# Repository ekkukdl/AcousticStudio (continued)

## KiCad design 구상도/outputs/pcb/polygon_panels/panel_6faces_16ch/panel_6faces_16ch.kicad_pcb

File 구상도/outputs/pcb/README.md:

# PCB 설계 및 업체 제출 자료

## 현재 8면 8기판 32채널 구성

현재 개발 기준은 한 기판 32채널, 같은 기판 8장, 총 256송신기입니다. [32채널 PCB R1 제작 자료](../panel_8faces_32ch_R1/README.md)와 [프레임 포함 Creo R2](../panel_8faces_32ch_R1/mechanical/creo32_frame_R2/사용안내.md)를 사용하세요. 아래 16채널 기판 16장의 업체 제출 자료는 이전 구성으로 보존한 것입니다.

## 이전 8면 16기판 요청

한 기판 16채널, 동일 기판 총 16장, 송신기 총 256개 구성입니다.

- [전체 납땜 요청 안내](polygon_panels/pcba_8faces_16boards/README_업로드_및_납땜요청.md)
- [DOILLABS 업로드 사용 안내](polygon_panels/pcba_8faces_16boards/DOILLABS/사용안내.txt)
- [업로드 BOM CSV](polygon_panels/pcba_8faces_16boards/DOILLABS/DOILLABS_BOM_8faces_16ch_UPLOAD.csv)
- [업로드 PnP CSV](polygon_panels/pcba_8faces_16boards/DOILLABS/DOILLABS_PnP_8faces_16ch_UPLOAD.csv)
- [업로드 BOM XLSX](polygon_panels/pcba_8faces_16boards/DOILLABS/DOILLABS_BOM_8faces_16ch_UPLOAD.xlsx)
- [업로드 PnP XLSX](polygon_panels/pcba_8faces_16boards/DOILLABS/DOILLABS_PnP_8faces_16ch_UPLOAD.xlsx)
- [8면용 Gerber ZIP](polygon_panels/pcba_8faces_16boards/panel_8faces_16ch_Gerber_P0_quote.zip)

DOILLABS에는 안내에 따라 `*_UPLOAD` 파일을 사용하세요. CSV와 같은 내용의 XLSX를 중복 제출하지 마세요. 접미사 없는 기존 XLSX와 기존 견적 ZIP은 이전 작성본으로 보존했으며 최신 UPLOAD 파일을 포함한다고 간주하지 마세요. 초음파 송신기 등 THT는 별도 수삽 작업으로 요청해야 합니다.

## KiCad 원본과 초기안

- [6면용 기판 원본](polygon_panels/panel_6faces_16ch/)
- [8면용 기판 원본](polygon_panels/panel_8faces_16ch/)
- [설계 설명](polygon_panels/설계설명_및_확인방법.md)
- [초기 Gerber ZIP](polygon_panels/gerber_quotes/)
- [초기 부품 견적](polygon_panels/부품견적_6면_8면.md)
- [초기 제조 및 추가 구매품 견적](polygon_panels/제작및추가부품견적_센서제외.md)

KiCad 프로젝트와 전용 심볼·풋프린트·3D 모델은 함께 보존했습니다. 기존 견적은 6면 6장 / 8면 8장 기준입니다. 현재 P0 자료의 간격 경고와 부품 방향 검토는 제조 승인 전에 필요합니다.

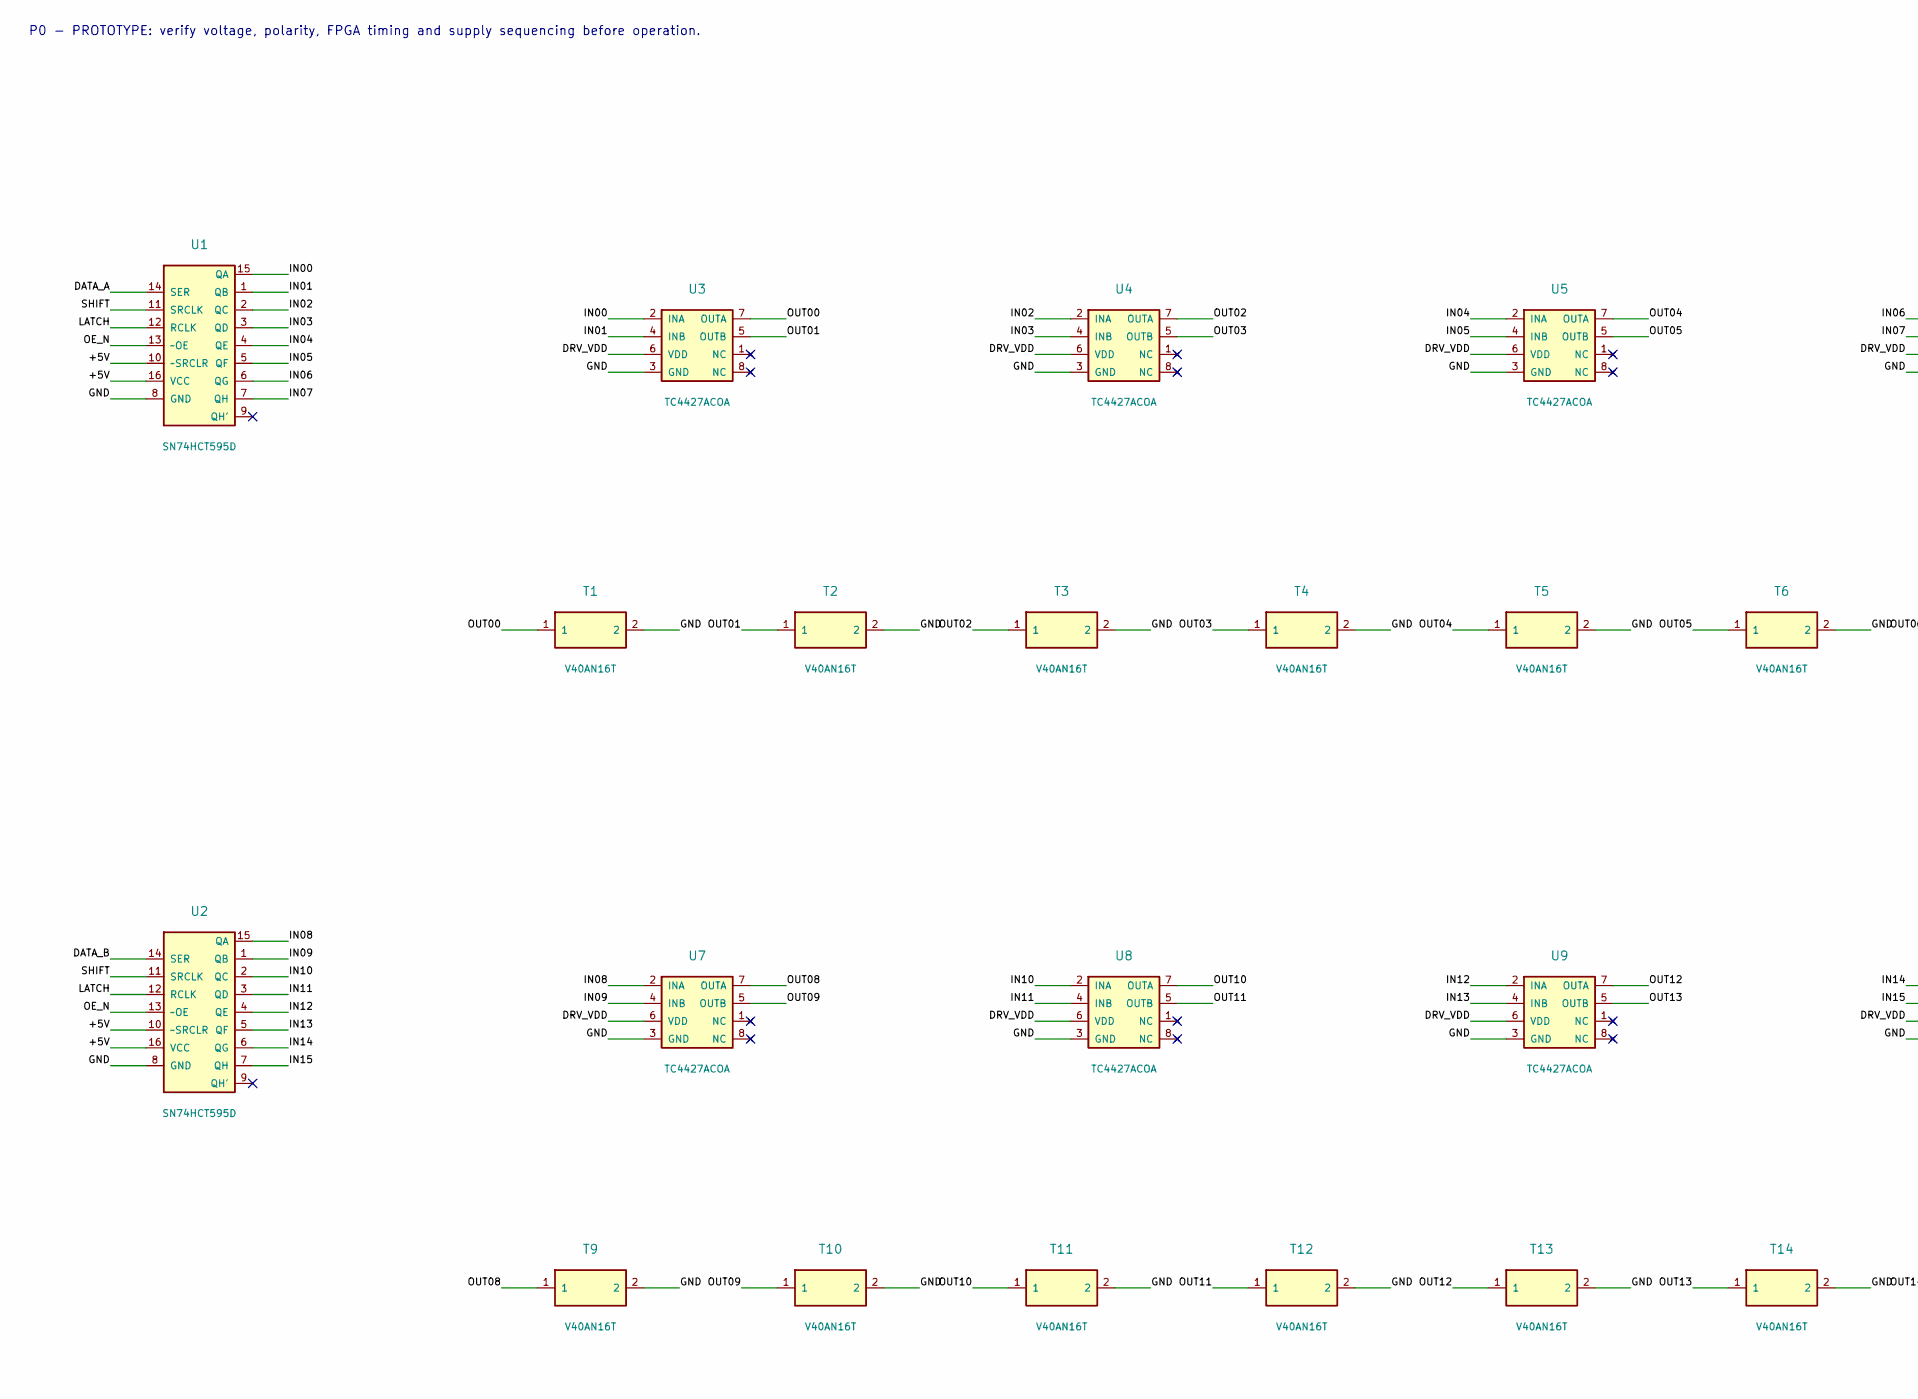
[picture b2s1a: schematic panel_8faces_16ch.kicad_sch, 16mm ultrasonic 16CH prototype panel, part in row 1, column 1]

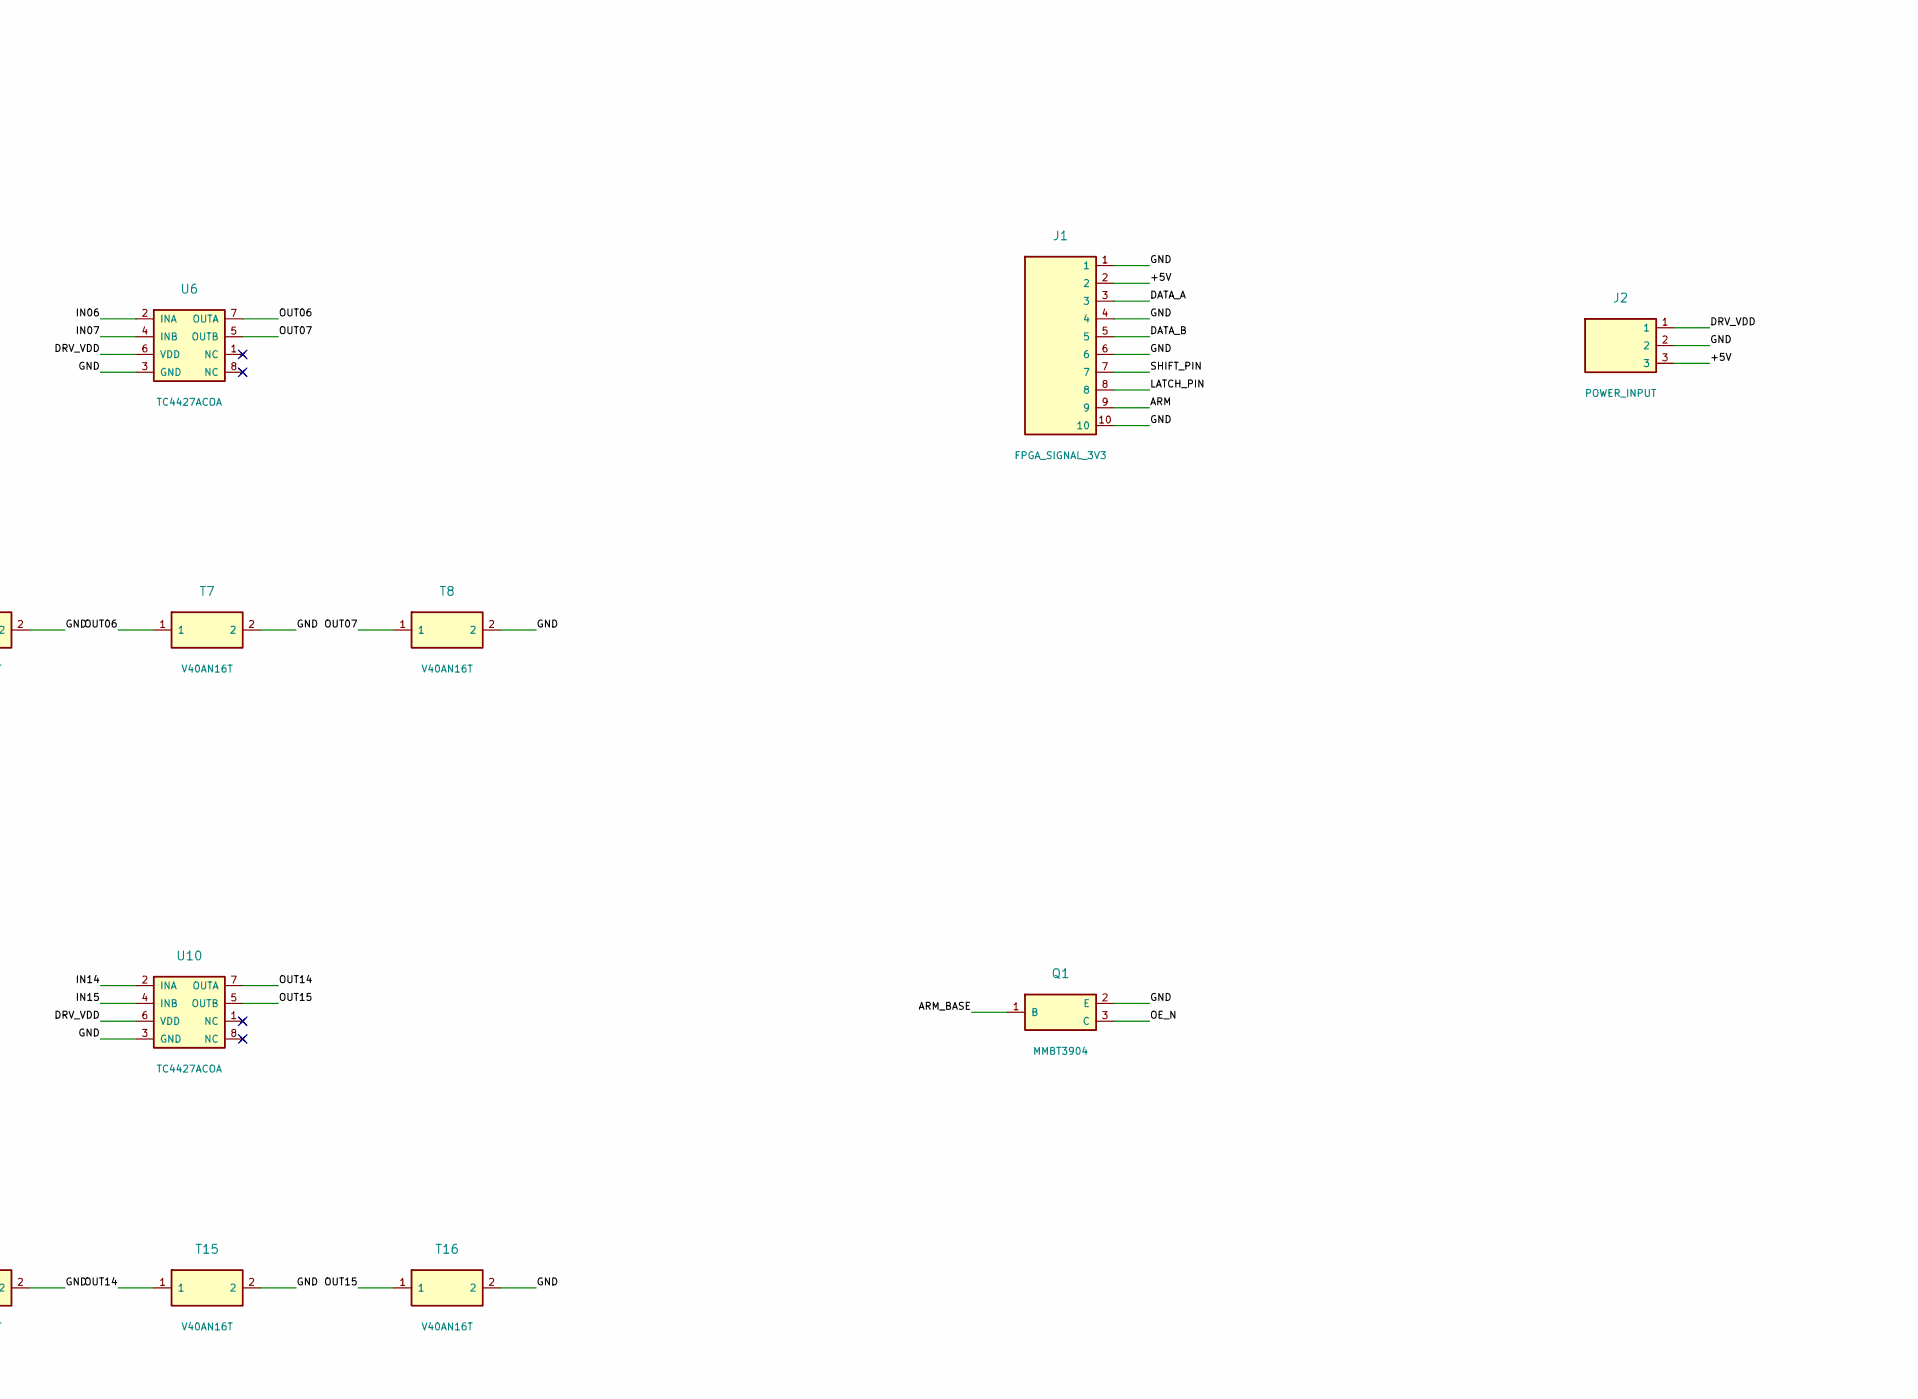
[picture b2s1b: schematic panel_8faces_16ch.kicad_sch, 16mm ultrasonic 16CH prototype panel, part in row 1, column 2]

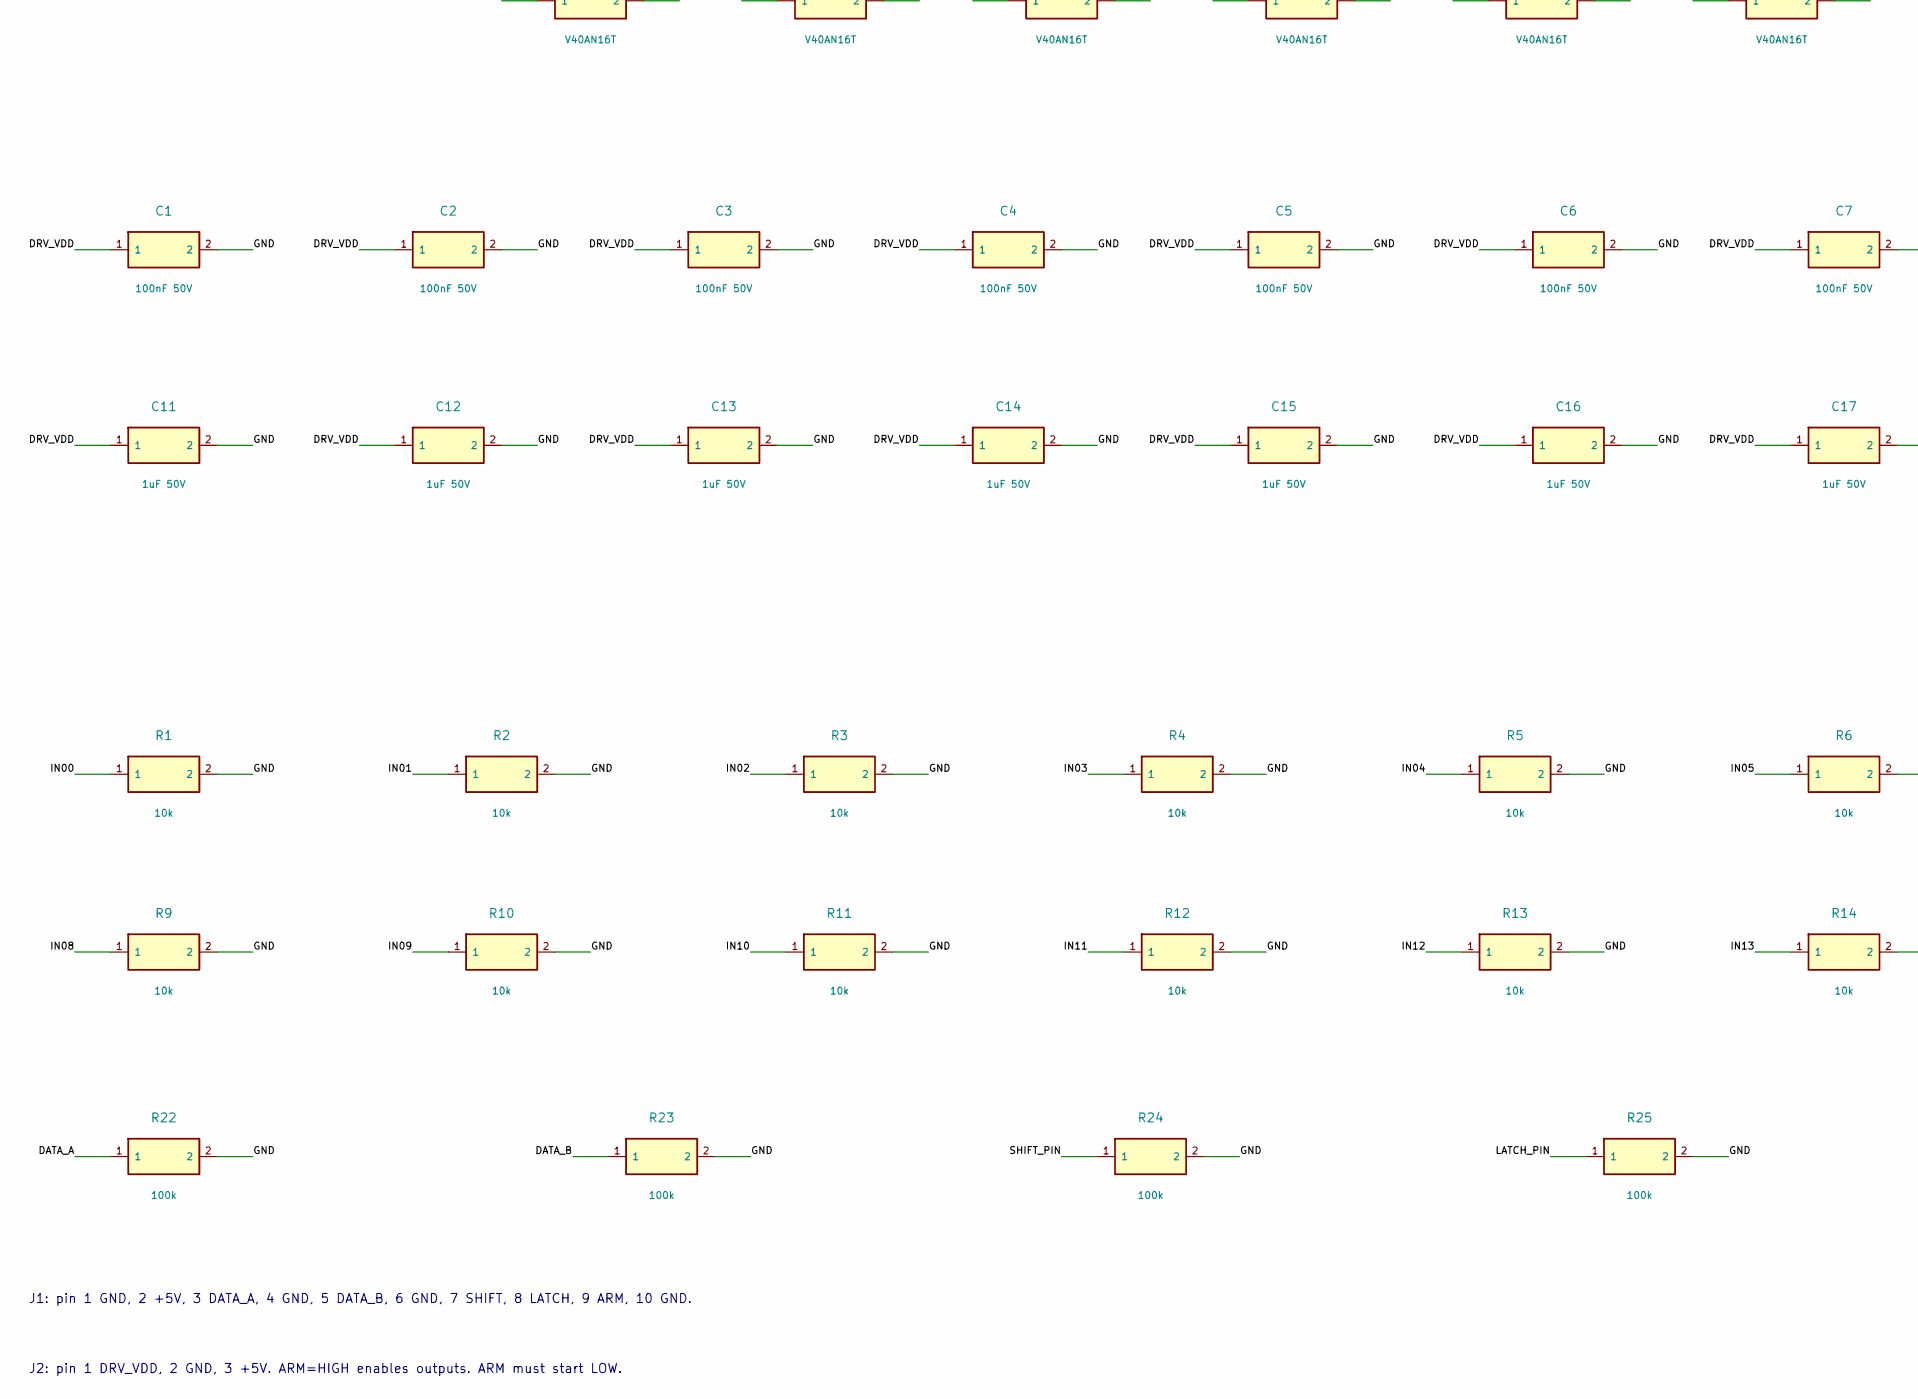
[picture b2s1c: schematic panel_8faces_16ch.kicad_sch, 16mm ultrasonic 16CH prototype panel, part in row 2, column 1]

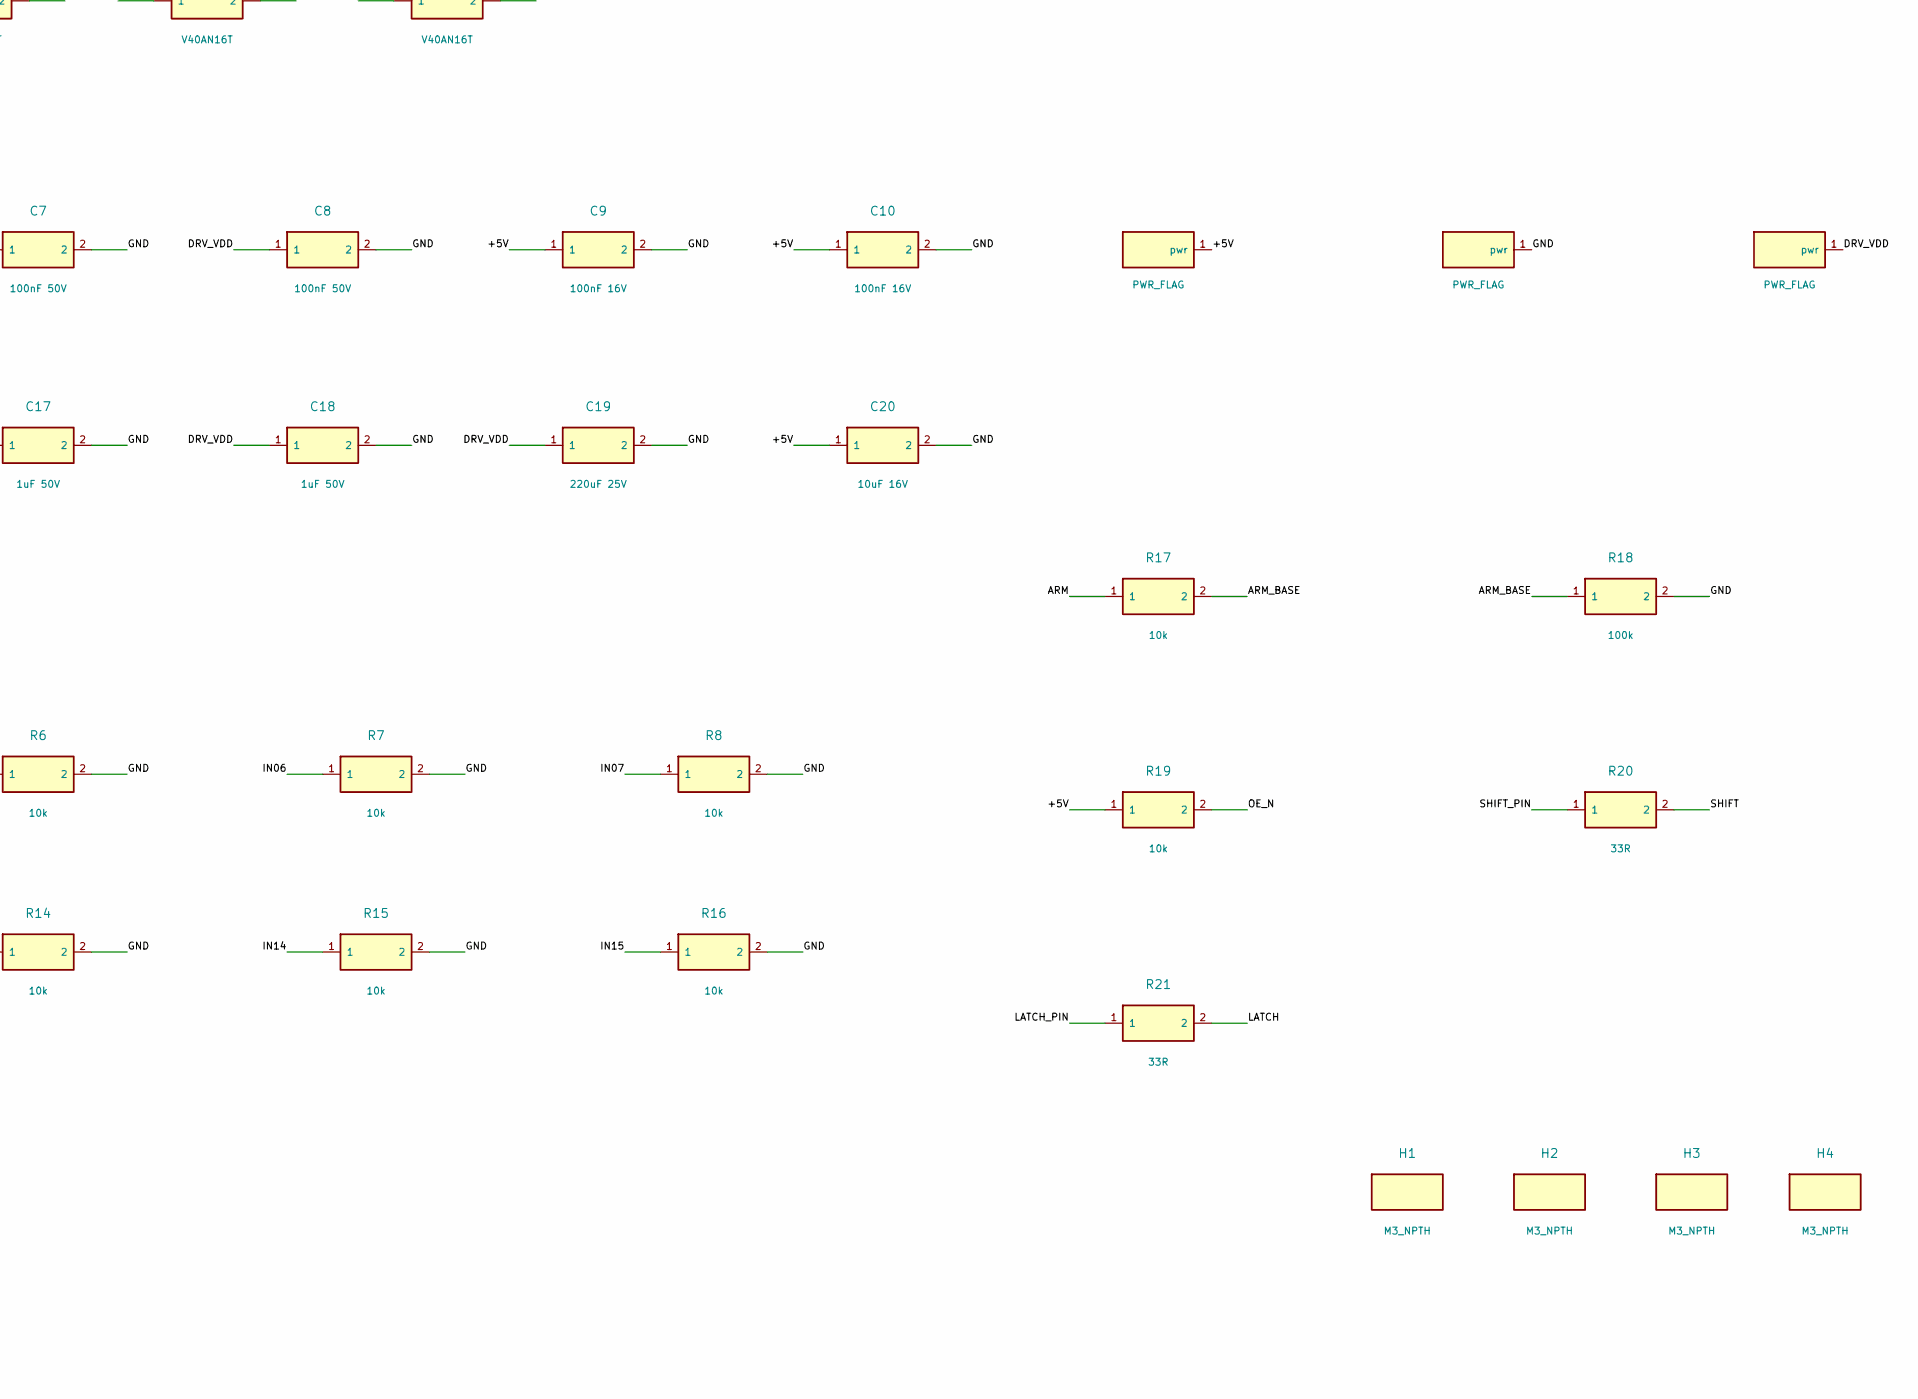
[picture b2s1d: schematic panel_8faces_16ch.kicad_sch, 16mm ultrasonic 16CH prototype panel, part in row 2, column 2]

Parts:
C1, C2, C3, C4, C5, C6, C7, C8: 100nF 50V; C0805
C9, C10: 100nF 16V; C0805
C11, C12, C13, C14, C15, C16, C17, C18: 1uF 50V; C0805
C19: 220uF 25V; CP_Radial_D6.3_P2.5
C20: 10uF 16V; C0805
H1, H2, H3, H4: M3_NPTH; Mount_M3
J1: FPGA_SIGNAL_3V3; Header2x05
J2: POWER_INPUT; Header1x03
Q1: MMBT3904; SOT23
R1, R2, R3, R4, R5, R6, R7, R8, R9, R10, R11, R12, R13, R14, R15, R16, R17, R19: 10k; R0805
R18, R22, R23, R24, R25: 100k; R0805
R20, R21: 33R; R0805
T1, T2, T3, T4, T5, T6, T7, T8, T9, T10, T11, T12, T13, T14, T15, T16: V40AN16T; V40AN16T_P10
U1, U2: SN74HCT595D; SOIC16
U3, U4, U5, U6, U7, U8, U9, U10: TC4427ACOA; SOIC8

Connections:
/+5V: C9.1, C10.1, C20.1, J1.2, J2.3, R19.1, U1.10 (~SRCLR), U1.16 (VCC), U2.10 (~SRCLR), U2.16 (VCC)
/ARM: J1.9, R17.1
/ARM_BASE: Q1.1 (B), R17.2, R18.1
/DATA_A: J1.3, R22.1, U1.14 (SER)
/DATA_B: J1.5, R23.1, U2.14 (SER)
/DRV_VDD: C1.1, C2.1, C3.1, C4.1, C5.1, C6.1, C7.1, C8.1, C11.1, C12.1, C13.1, C14.1, C15.1, C16.1, C17.1, C18.1, C19.1, J2.1, U3.6 (VDD), U4.6 (VDD), U5.6 (VDD), U6.6 (VDD), U7.6 (VDD), U8.6 (VDD), U9.6 (VDD), U10.6 (VDD)
/GND: C1.2, C2.2, C3.2, C4.2, C5.2, C6.2, C7.2, C8.2, C9.2, C10.2, C11.2, C12.2, C13.2, C14.2, C15.2, C16.2, C17.2, C18.2, C19.2, C20.2, J1.1, J1.4, J1.6, J1.10, J2.2, Q1.2 (E), R1.2, R2.2, R3.2, R4.2, R5.2, R6.2, R7.2, R8.2, R9.2, R10.2, R11.2, R12.2, R13.2, R14.2, R15.2, R16.2, R18.2, R22.2, R23.2, R24.2, R25.2, T1.2, T2.2, T3.2, T4.2, T5.2, T6.2, T7.2, T8.2, T9.2, T10.2, T11.2, T12.2, T13.2, T14.2, T15.2, T16.2, U1.8 (GND), U2.8 (GND), U3.3 (GND), U4.3 (GND), U5.3 (GND), U6.3 (GND), U7.3 (GND), U8.3 (GND), U9.3 (GND), U10.3 (GND)
/IN00: R1.1, U1.15 (QA), U3.2 (INA)
/IN01: R2.1, U1.1 (QB), U3.4 (INB)
/IN02: R3.1, U1.2 (QC), U4.2 (INA)
/IN03: R4.1, U1.3 (QD), U4.4 (INB)
/IN04: R5.1, U1.4 (QE), U5.2 (INA)
/IN05: R6.1, U1.5 (QF), U5.4 (INB)
/IN06: R7.1, U1.6 (QG), U6.2 (INA)
/IN07: R8.1, U1.7 (QH), U6.4 (INB)
/IN08: R9.1, U2.15 (QA), U7.2 (INA)
/IN09: R10.1, U2.1 (QB), U7.4 (INB)
/IN10: R11.1, U2.2 (QC), U8.2 (INA)
/IN11: R12.1, U2.3 (QD), U8.4 (INB)
/IN12: R13.1, U2.4 (QE), U9.2 (INA)
/IN13: R14.1, U2.5 (QF), U9.4 (INB)
/IN14: R15.1, U2.6 (QG), U10.2 (INA)
/IN15: R16.1, U2.7 (QH), U10.4 (INB)
/LATCH: R21.2, U1.12 (RCLK), U2.12 (RCLK)
/LATCH_PIN: J1.8, R21.1, R25.1
/OE_N: Q1.3 (C), R19.2, U1.13 (~OE), U2.13 (~OE)
/OUT00: T1.1, U3.7 (OUTA)
/OUT01: T2.1, U3.5 (OUTB)
/OUT02: T3.1, U4.7 (OUTA)
/OUT03: T4.1, U4.5 (OUTB)
/OUT04: T5.1, U5.7 (OUTA)
/OUT05: T6.1, U5.5 (OUTB)
/OUT06: T7.1, U6.7 (OUTA)
/OUT07: T8.1, U6.5 (OUTB)
/OUT08: T9.1, U7.7 (OUTA)
/OUT09: T10.1, U7.5 (OUTB)
/OUT10: T11.1, U8.7 (OUTA)
/OUT11: T12.1, U8.5 (OUTB)
/OUT12: T13.1, U9.7 (OUTA)
/OUT13: T14.1, U9.5 (OUTB)
/OUT14: T15.1, U10.7 (OUTA)
/OUT15: T16.1, U10.5 (OUTB)
/SHIFT: R20.2, U1.11 (SRCLK), U2.11 (SRCLK)
/SHIFT_PIN: J1.7, R20.1, R24.1

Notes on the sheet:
P0 - PROTOTYPE: verify voltage, polarity, FPGA timing and supply sequencing before operation.
J1: pin 1 GND, 2 +5V, 3 DATA_A, 4 GND, 5 DATA_B, 6 GND, 7 SHIFT, 8 LATCH, 9 ARM, 10 GND.
J2: pin 1 DRV_VDD, 2 GND, 3 +5V. ARM=HIGH enables outputs. ARM must start LOW.

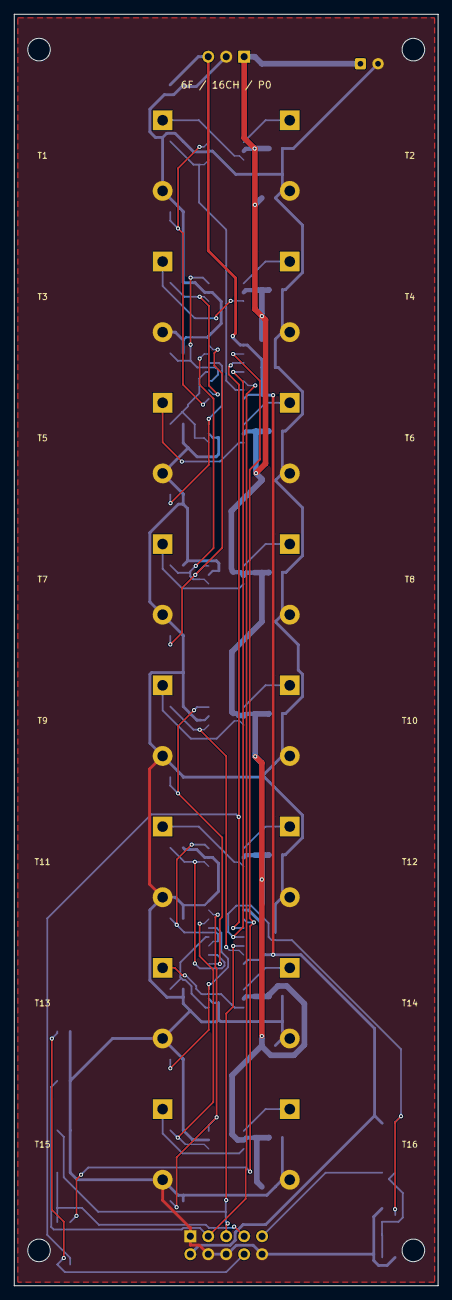
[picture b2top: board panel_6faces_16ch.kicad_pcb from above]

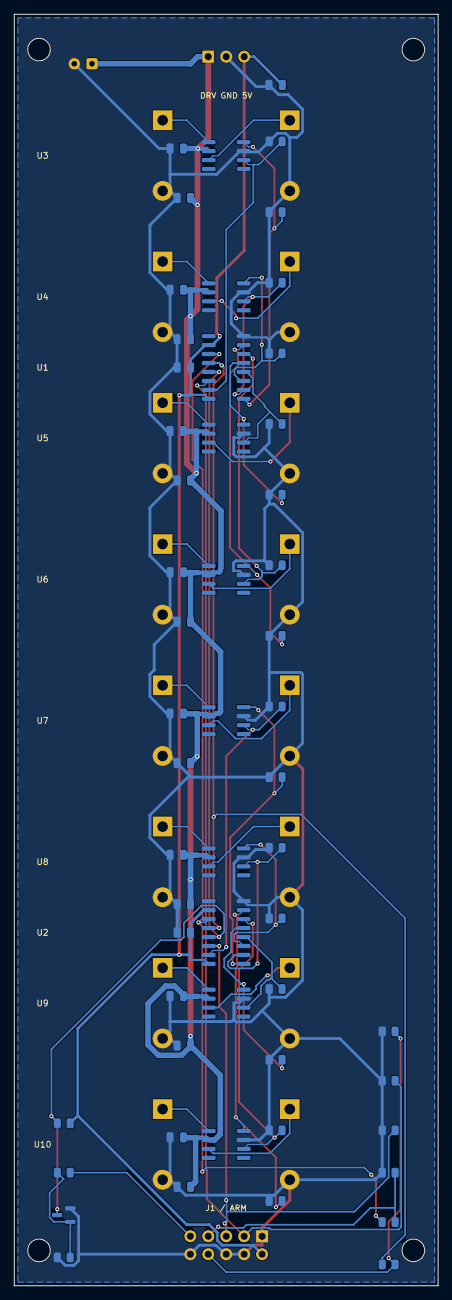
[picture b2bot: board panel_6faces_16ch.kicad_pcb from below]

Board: 2 copper layers, 60.0 x 180.0 mm, 78 parts (58 on the bottom side), 44 nets.

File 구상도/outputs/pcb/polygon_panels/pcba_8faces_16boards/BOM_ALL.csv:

Comment,Designator,Footprint,Manufacturer,MPN,LCSC Part #,Quantity
100nF 50V X7R 10% 0805,"C1,C2,C3,C4,C5,C6,C7,C8,C9,C10",C0805,YAGEO,CC0805KRX7R9BB104,C49678,10
1uF 50V X7R 10% 0805,"C11,C12,C13,C14,C15,C16,C17,C18",C0805,CCTC,TCC0805X7R105K500DT,C376926,8
10uF >=16V 0805,C20,C0805,Murata,GRM21BR61E106KA73L,,1
220uF 25V radial D6.3mm P2.5mm,C19,CP_Radial_D6.3_P2.5,Rubycon,25YXJ220M6.3X11,C88729,1
10k 1% 0805 0.125W,"R1,R2,R3,R4,R5,R6,R7,R8,R9,R10,R11,R12,R13,R14,R15,R16,R17,R19",R0805,YAGEO,RC0805FR-0710KL,,18
100k 1% 0805 0.125W,"R18,R22,R23,R24,R25",R0805,YAGEO,RC0805FR-07100KL,,5
33 ohm 1% 0805 0.125W,"R20,R21",R0805,YAGEO,RC0805FR-0733RL,,2
74HCT595 SO16 shift register,"U1,U2",SOIC16,Nexperia,"74HCT595D,118",C282339,2
TC4427A dual non-inverting driver SOIC8,"U3,U4,U5,U6,U7,U8,U9,U10",SOIC8,Microchip,TC4427ACOA713,C144234,8
MMBT3904 NPN SOT23,Q1,SOT23,Nexperia,"MMBT3904,215",,1
Male straight header 2x5 P2.54mm,J1,Header2x05,Vendor selection,,,1
Male straight header 1x3 P2.54mm,J2,Header1x03,Vendor selection,,,1
40kHz transmitter D16mm pin pitch 10mm,"T1,T2,T3,T4,T5,T6,T7,T8,T9,T10,T11,T12,T13,T14,T15,T16",V40AN16T_P10,Supplier confirmation,,,16
